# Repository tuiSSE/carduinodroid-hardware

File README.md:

# carduinodroid-hardware

For further information take a look at the carduinodroid-wiki:

https://github.com/tuiSSE/carduinodroid-wiki/wiki

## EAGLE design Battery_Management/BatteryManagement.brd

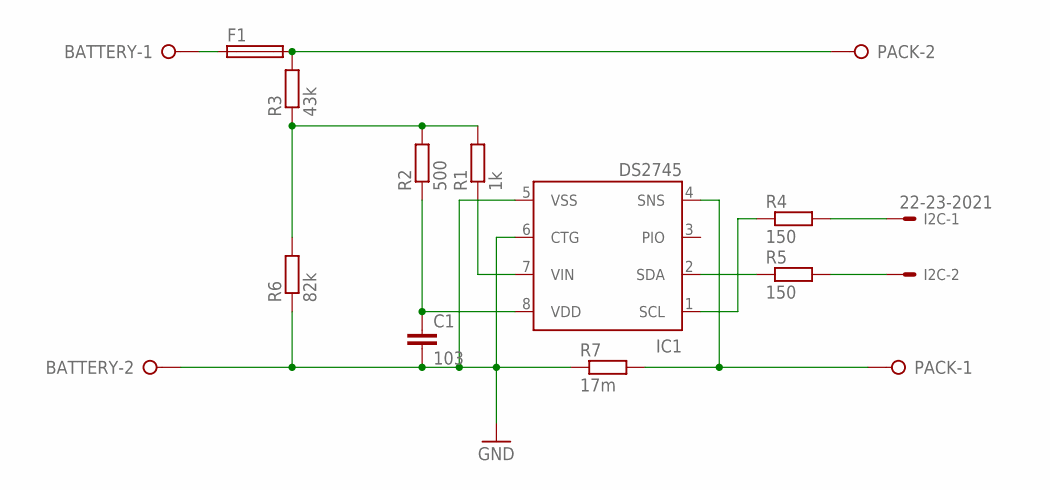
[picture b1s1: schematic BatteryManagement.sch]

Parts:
BATTERY: W237-02P; W237-132
C1: 103; C050-030X075
F1: SH22,5
I2C: 22-23-2021
IC1: DS2745; UMAX10
PACK: W237-02P; W237-132
R1: 1k; 0207/10
R2: 500; 0207/10
R3: 43k; 0207/10
R4, R5: 150; 0207/10
R6: 82k; 0207/10
R7: 17m; M1206

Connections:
GND: BATTERY.2, C1.2, IC1.5 (VSS), IC1.6 (CTG), R6.1, R7.1
unnamed: I2C.1, R4.2
unnamed: I2C.2, R5.2
unnamed: IC1.1 (SCL), R4.1
unnamed: IC1.2 (SDA), R5.1
unnamed: BATTERY.1, F1.1
unnamed: IC1.7 (VIN), R1.1
unnamed: C1.1, IC1.8 (VDD), R2.1
unnamed: IC1.4 (SNS), PACK.1, R7.2
unnamed: F1.2, PACK.2, R3.2
unnamed: R1.2, R2.2, R3.1, R6.2

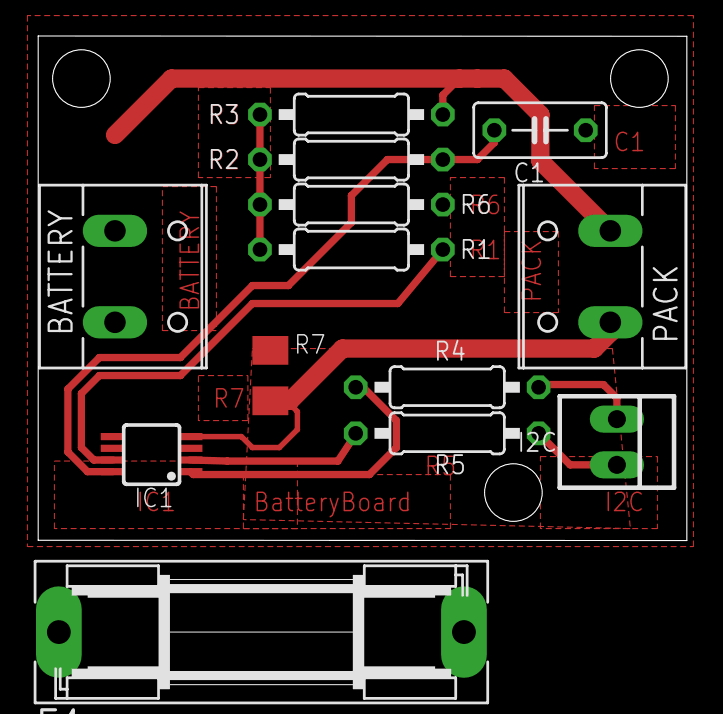
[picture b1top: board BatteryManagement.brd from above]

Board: 2 copper layers, 36.0 x 28.0 mm, 13 parts (0 on the bottom side), 11 nets.

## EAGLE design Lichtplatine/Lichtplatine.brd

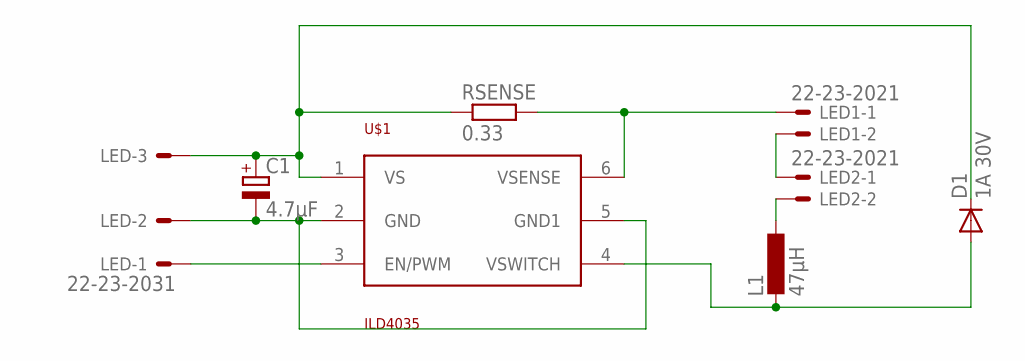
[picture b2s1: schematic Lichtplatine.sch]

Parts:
C1: 4.7µF; E2,5-5
D1: 1A 30V; DO41-7.6
L1: 47µH; 6000-XXXX-RC
LED: 22-23-2031
LED1, LED2: 22-23-2021
RSENSE: 0.33; R2010
U$1: ILD4035; SC74

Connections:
GND: C1.-, LED.2, U$1.2 (GND), U$1.5 (GND1)
unnamed: LED.1, U$1.3 (EN/PWM)
unnamed: C1.+, D1.C, LED.3, RSENSE.1, U$1.1 (VS)
unnamed: LED1.2, LED2.1
unnamed: L1.1, LED2.2
unnamed: LED1.1, RSENSE.2, U$1.6 (VSENSE)
unnamed: D1.A, L1.2, U$1.4 (VSWITCH)

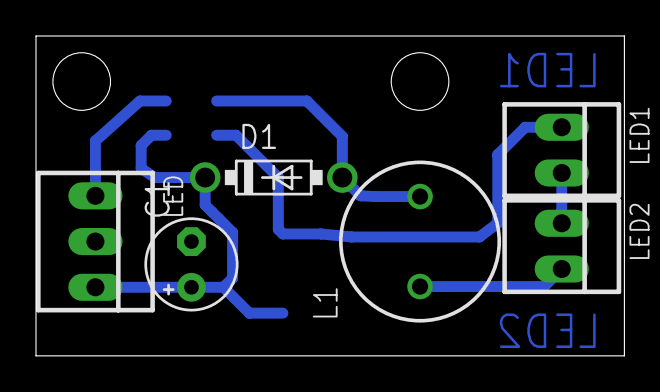
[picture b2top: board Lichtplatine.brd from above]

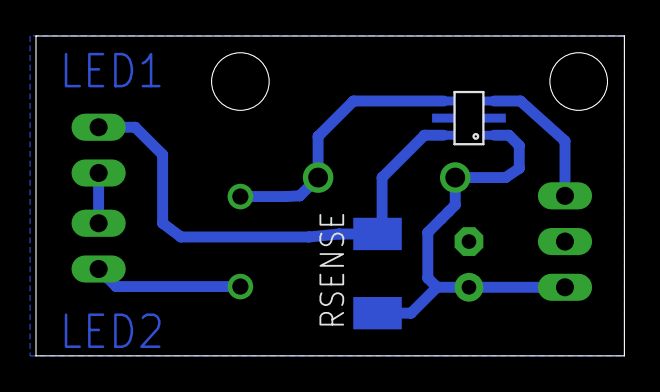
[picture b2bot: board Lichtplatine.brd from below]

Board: 2 copper layers, 32.7 x 17.8 mm, 8 parts (2 on the bottom side), 7 nets.

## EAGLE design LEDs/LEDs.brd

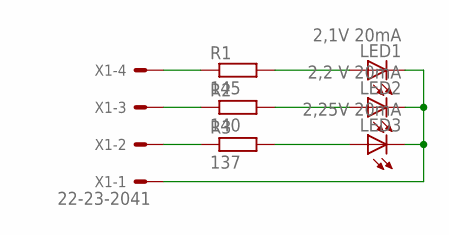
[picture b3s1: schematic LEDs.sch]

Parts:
LED1: 2,1V 20mA; LED5MM
LED2: 2,2 V 20mA; LED5MM
LED3: 2,25V 20mA; LED5MM
R1: 145; 0207/10
R2: 140; 0207/10
R3: 137; 0207/10
X1: 22-23-2041

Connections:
GND: LED1.K (C), LED2.K (C), LED3.K (C), X1.1
unnamed: R1.1, X1.4
unnamed: R2.1, X1.3
unnamed: R3.1, X1.2
unnamed: LED1.A, R1.2
unnamed: LED2.A, R2.2
unnamed: LED3.A, R3.2

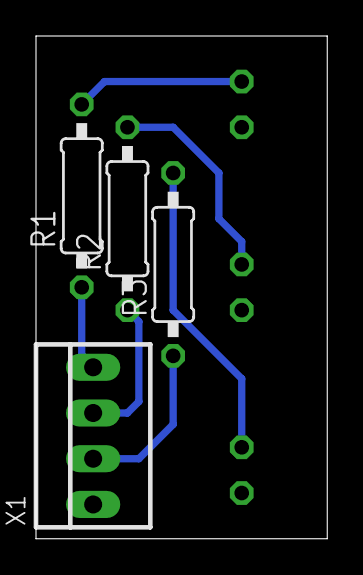
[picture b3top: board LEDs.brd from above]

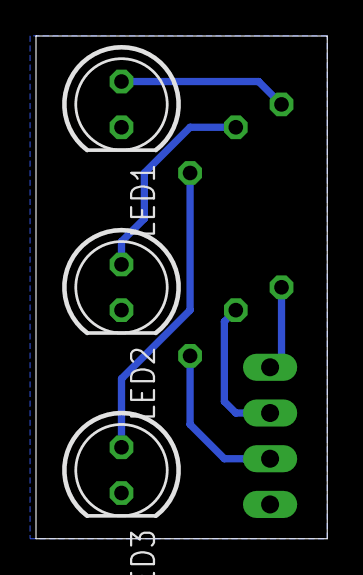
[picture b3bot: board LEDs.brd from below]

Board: 2 copper layers, 16.2 x 27.9 mm, 7 parts (3 on the bottom side), 7 nets.

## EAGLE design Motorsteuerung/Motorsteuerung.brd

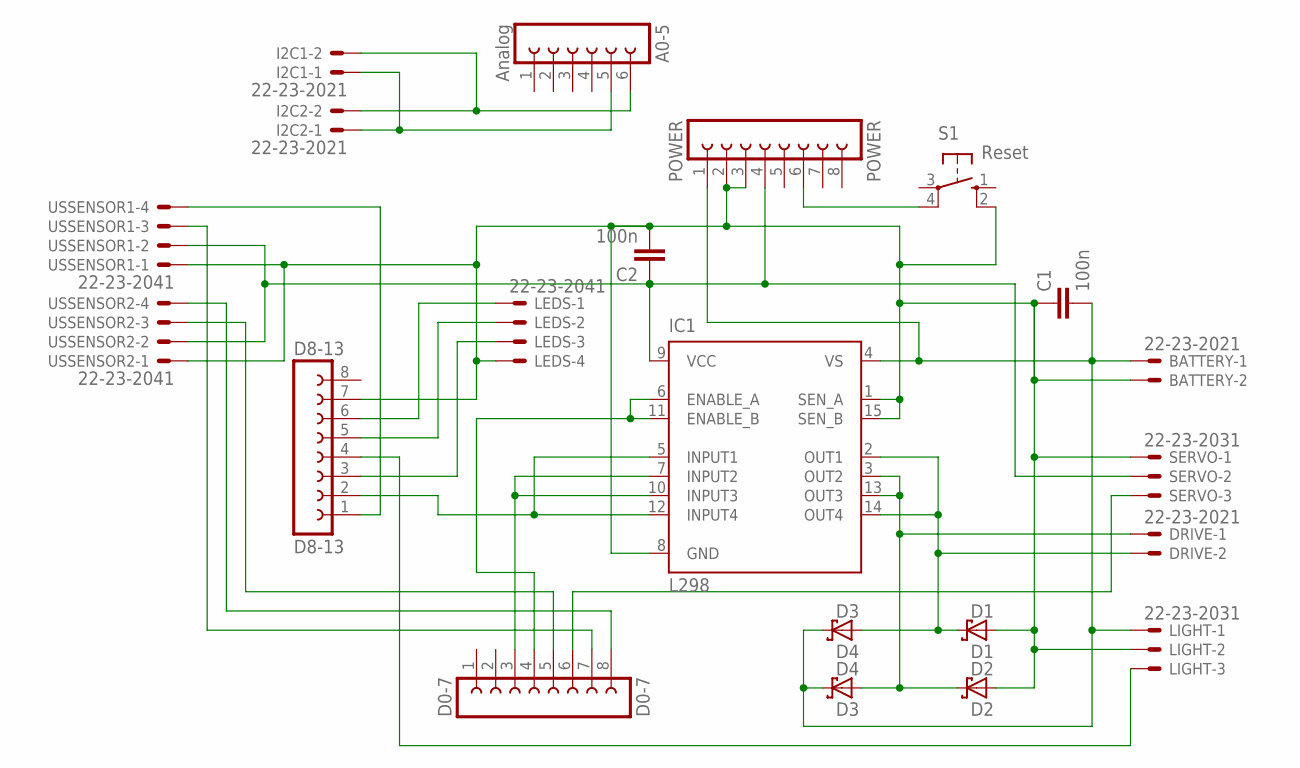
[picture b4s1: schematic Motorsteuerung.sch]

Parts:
A0-5: Analog; FE06
BATTERY: 22-23-2021
C1, C2: 100n; C025-030X050
D0-7: D0-7; FE08
D1: D1; DO201T15
D2: D2; DO201T15
D3: D4; DO201T15
D4: D3; DO201T15
D8-13: D8-13; FE08
DRIVE: 22-23-2021
I2C1: 22-23-2021
I2C2: 22-23-2021; MPN 22-23-2021
IC1: L298; MULTIWATT-15
LEDS: 22-23-2041
LIGHT: 22-23-2031
POWER: POWER; FE08
S1: Reset; B3F-10XX
SERVO: 22-23-2031
USSENSOR1, USSENSOR2: 22-23-2041; MPN 22-23-2041

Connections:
GND: BATTERY.2, C1.1, C2.2, D1.A, D2.A, D8-13.7, IC1.1 (SEN_A), IC1.8 (GND), IC1.15 (SEN_B), LEDS.4, LIGHT.2, POWER.2, POWER.3, S1.2 (S1), SERVO.1, USSENSOR1.1, USSENSOR2.1
unnamed: D1.C, D4.A, DRIVE.2, IC1.2 (OUT1), IC1.14 (OUT4)
unnamed: D0-7.6, SERVO.3
unnamed: D0-7.8, USSENSOR2.4
unnamed: D2.C, D3.A, DRIVE.1, IC1.3 (OUT2), IC1.13 (OUT3)
unnamed: D8-13.5, LEDS.2
unnamed: D8-13.2, IC1.5 (INPUT1), IC1.12 (INPUT4)
unnamed: D0-7.5, USSENSOR2.3
unnamed: D0-7.3, IC1.7 (INPUT2), IC1.10 (INPUT3)
unnamed: D0-7.4, IC1.6 (ENABLE_A), IC1.11 (ENABLE_B)
unnamed: D8-13.1, USSENSOR1.4
unnamed: D8-13.3, LEDS.3
unnamed: D8-13.4, LIGHT.3
unnamed: D8-13.6, LEDS.1
unnamed: D0-7.7, USSENSOR1.3
unnamed: A0-5.5, I2C1.1, I2C2.1
unnamed: POWER.6, S1.4 (P1)
unnamed: A0-5.6, I2C1.2, I2C2.2
VCC: C2.1, IC1.9 (VCC), POWER.4, SERVO.2, USSENSOR1.2, USSENSOR2.2
VS: BATTERY.1, C1.2, D3.C, D4.C, IC1.4 (VS), LIGHT.1, POWER.1

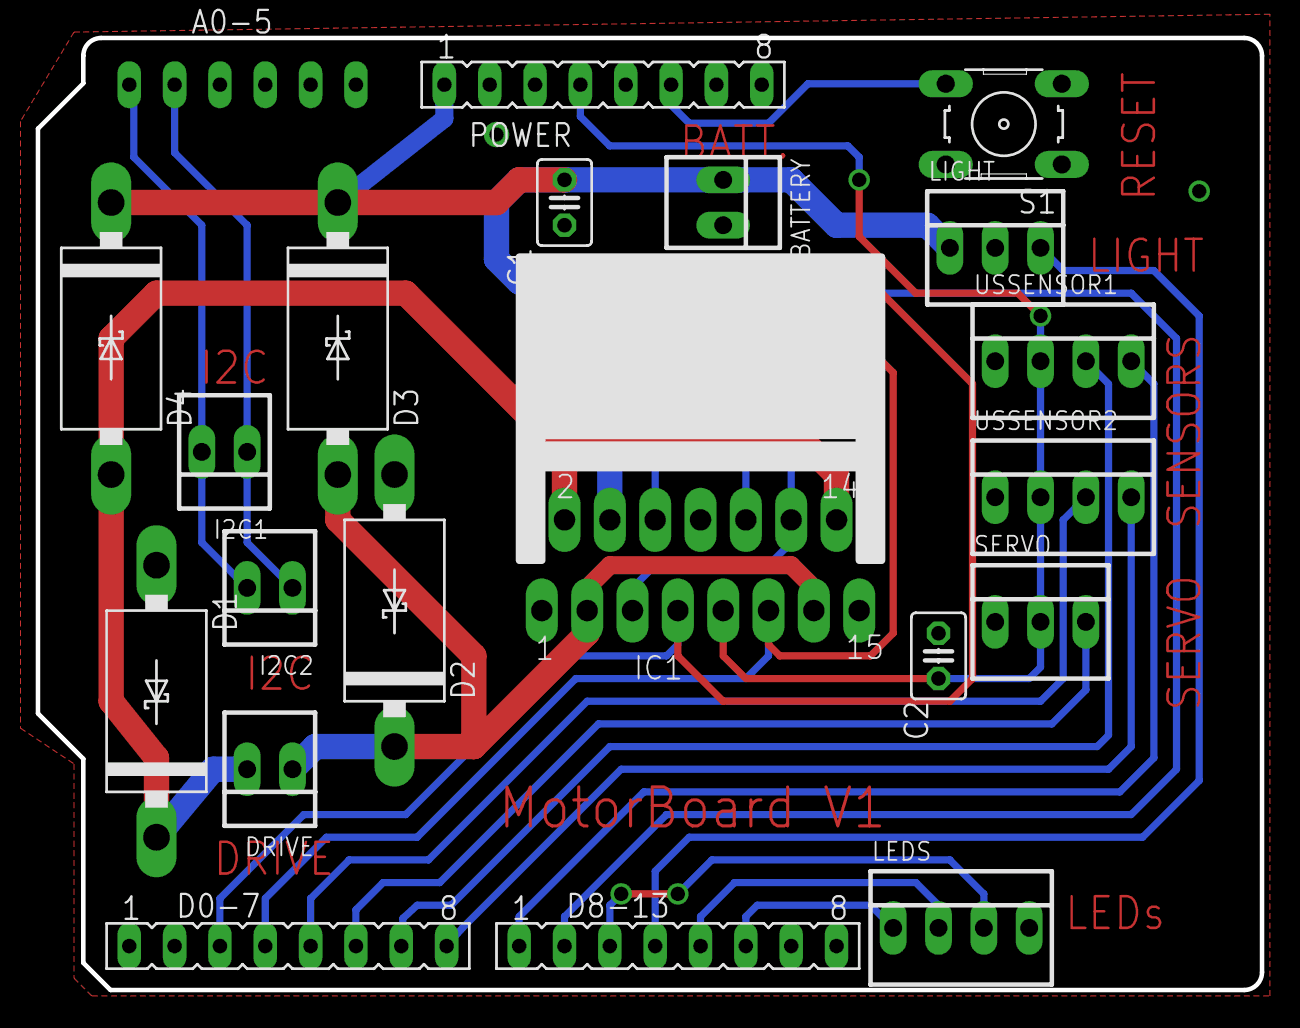
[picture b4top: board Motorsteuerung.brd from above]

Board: 2 copper layers, 68.6 x 53.3 mm, 21 parts (1 on the bottom side), 20 nets.

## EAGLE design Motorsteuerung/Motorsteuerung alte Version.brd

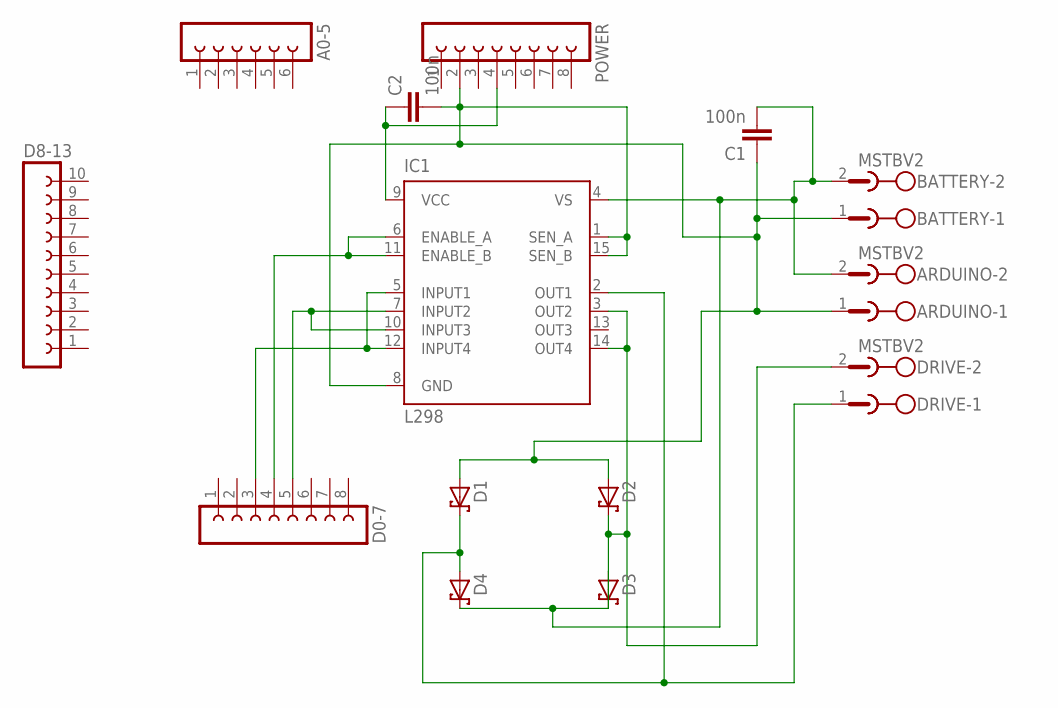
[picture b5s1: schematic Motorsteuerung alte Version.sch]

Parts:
A0-5: FE06-1; FE06
ARDUINO: MSTBV2
BATTERY: MSTBV2
C1, C2: 100n; C025-030X050
D0-7: FE08-1; FE08
D1, D2, D3, D4: SCHOTTKY-DIODEDO201T15; DO201T15
D8-13: FE10-1; FE10
DRIVE: MSTBV2
IC1: L298; MULTIWATT-15
POWER: FE08-1; FE08

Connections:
unnamed: D1.C, D4.A, DRIVE.1, IC1.2 (OUT1)
unnamed: ARDUINO.2, BATTERY.2, C1.2, D3.C, D4.C, IC1.4 (VS)
unnamed: D2.C, D3.A, DRIVE.2, IC1.3 (OUT2), IC1.14 (OUT4)
unnamed: C2.1, IC1.9 (VCC), POWER.4
unnamed: D0-7.3, IC1.5 (INPUT1), IC1.12 (INPUT4)
unnamed: ARDUINO.1, BATTERY.1, C1.1, C2.2, D1.A, D2.A, IC1.1 (SEN_A), IC1.8 (GND), IC1.15 (SEN_B), POWER.2
unnamed: D0-7.5, IC1.7 (INPUT2), IC1.10 (INPUT3)
unnamed: D0-7.4, IC1.6 (ENABLE_A), IC1.11 (ENABLE_B)

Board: 2 copper layers, 14 parts (1 on the bottom side), 8 nets, no tracks yet.

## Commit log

2015-04-23 First Checkout
